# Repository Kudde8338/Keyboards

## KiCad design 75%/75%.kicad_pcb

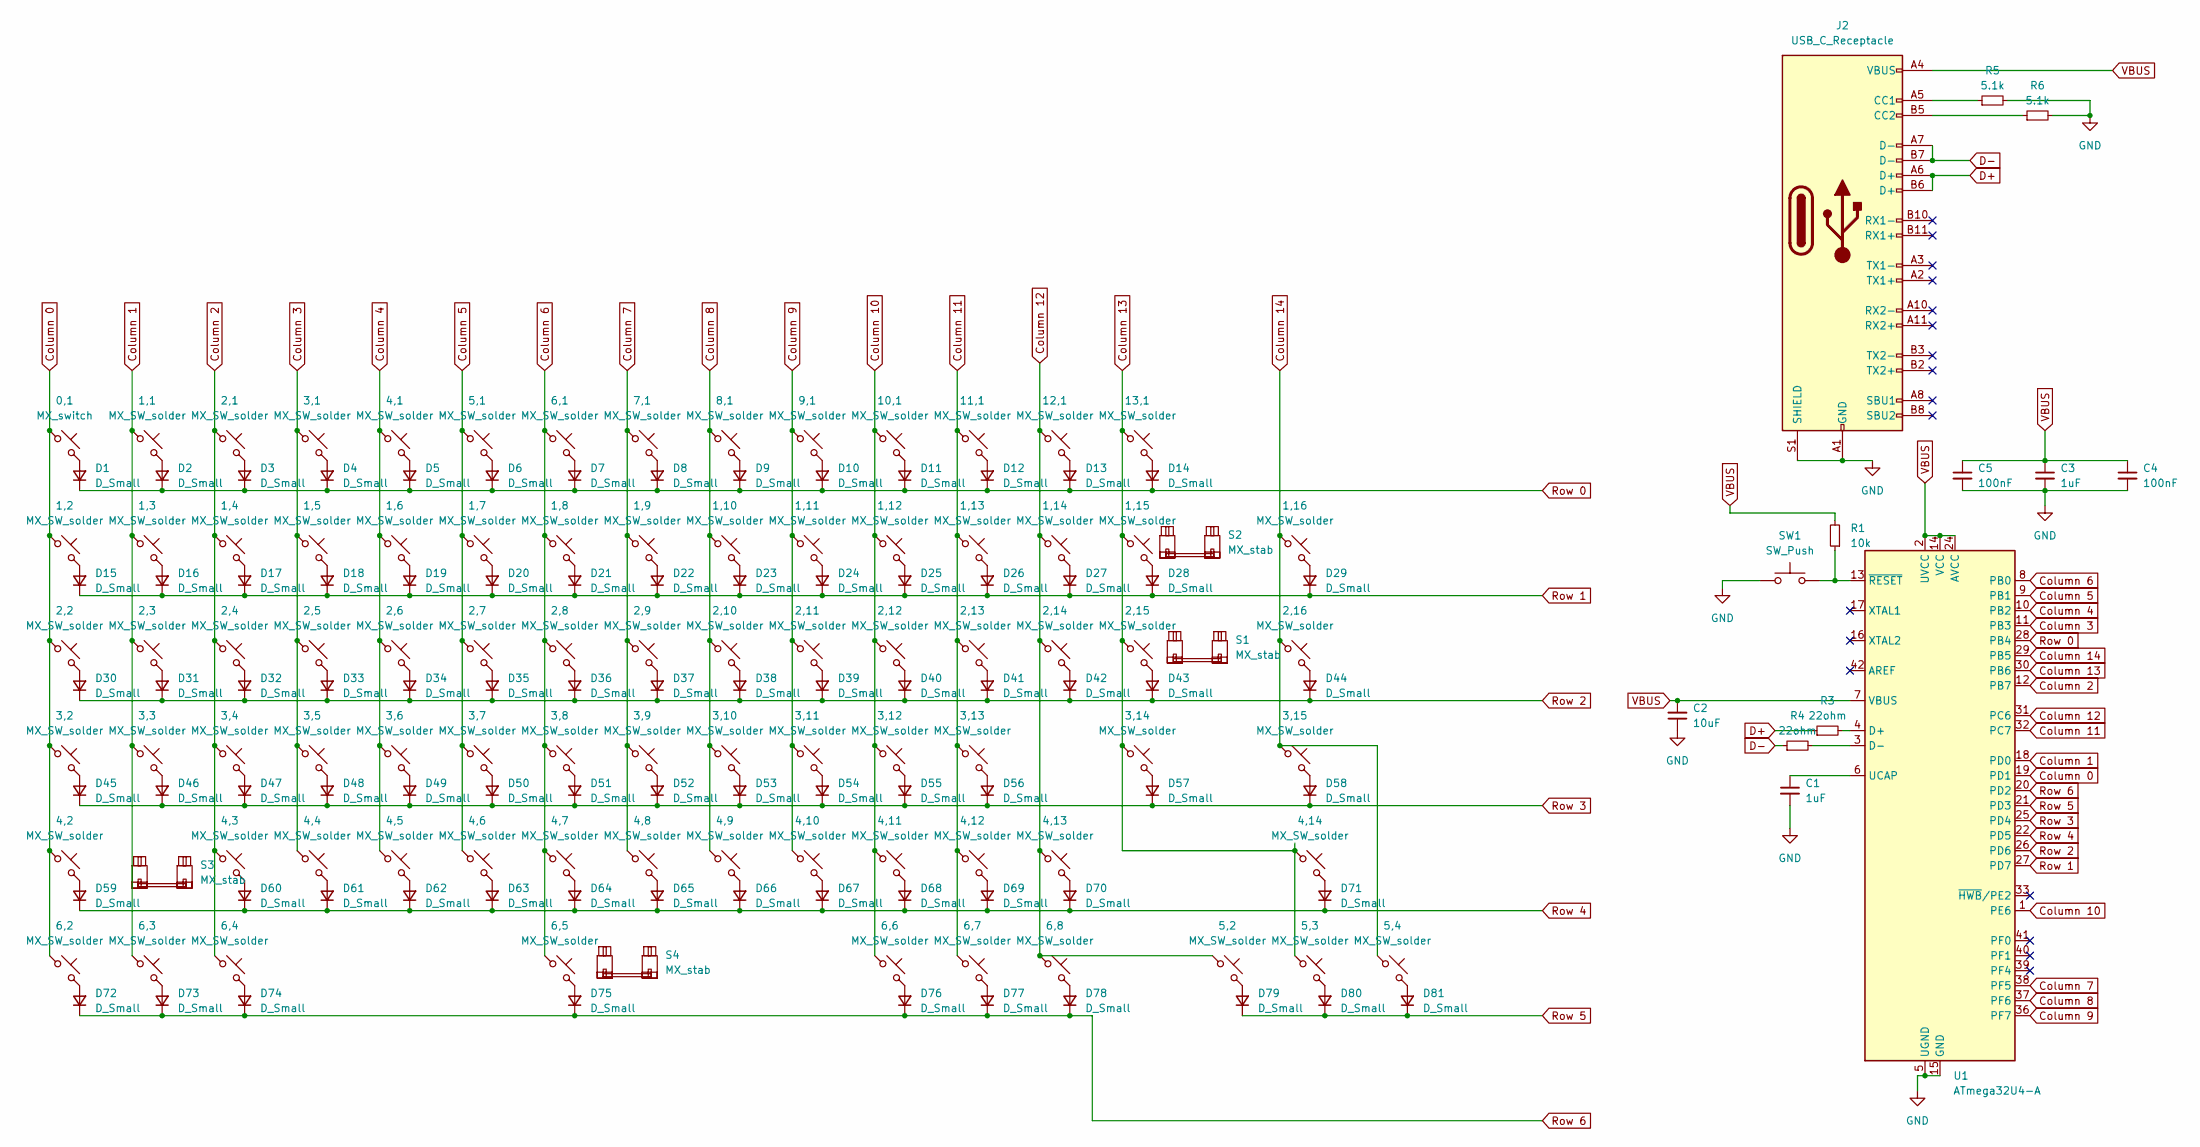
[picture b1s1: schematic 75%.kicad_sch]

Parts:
0,1: MX_switch; SW_MX_1u
1,1, 1,2, 1,3, 1,4, 1,5, 1,6, 1,7, 1,8, 1,9, 1,10, 1,11, 1,12, 1,13, 1,14, 1,15, 1,16, 2,1, 2,3, 2,4, 2,5, 2,6, 2,7, 2,8, 2,9, 2,10, 2,11, 2,12, 2,13, 2,14, 2,16, 3,1, 3,3, 3,4, 3,5, 3,6, 3,7, 3,8, 3,9, 3,10, 3,11, 3,12, 3,13, 3,14, 3,15, 4,1, 4,2, 4,3, 4,4, 4,5, 4,6, 4,7, 4,8, 4,9, 4,10, 4,11, 4,12, 4,14, 5,1, 5,2, 5,3, 5,4, 6,1, 6,5, 6,6, 6,7, 6,8, 7,1, 8,1, 9,1, 10,1, 11,1, 12,1, 13,1: MX_SW_solder; SW_MX_1u
2,2, 2,15: MX_SW_solder; SW_MX_1.5u
3,2, 4,13: MX_SW_solder; SW_MX_1.75u
6,2, 6,3, 6,4: MX_SW_solder; SW_MX_1.25u
C1, C3: 1uF; C_0805_2012Metric
C2: 10uF; C_0805_2012Metric
C4, C5: 100nF; C_0805_2012Metric
D1, D2, D3, D4, D5, D6, D7, D8, D9, D10, D11, D12, D13, D14, D15, D16, D17, D18, D19, D20, D21, D22, D23, D24, D25, D26, D27, D28, D29, D30, D31, D32, D33, D34, D35, D36, D37, D38, D39, D40, D41, D42, D43, D44, D45, D46, D47, D48, D49, D50, D51, D52, D53, D54, D55, D56, D57, D58, D59, D60, D61, D62, D63, D64, D65, D66, D67, D68, D69, D70, D71, D72, D73, D74, D75, D76, D77, D78, D79, D80, D81: D_Small; D_SOD-123
J2: USB_C_Receptacle; USB_C_Receptacle_GCT_USB4105-xx-A_16P_TopMnt_Horizontal
R1: 10k; R_0805_2012Metric
R3, R4: 22ohm; R_0805_2012Metric
R5, R6: 5.1k; R_0805_2012Metric
S1, S3: MX_stab; STAB_MX_P_2.25u
S2: MX_stab; STAB_MX_P_2u
S4: MX_stab; STAB_MX_P_6.25u
SW1: SW_Push; SW_PUSH-12mm
U1: ATmega32U4-A; TQFP-44_10x10mm_P0.8mm

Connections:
Column 0: 0,1.1, 1,2.1, 2,2.1, 3,2.1, 4,2.1, 6,2.1, U1.19 (PD1)
Column 1: 1,1.1, 1,3.1, 2,3.1, 3,3.1, 6,3.1, U1.18 (PD0)
Column 2: 1,4.1, 2,1.1, 2,4.1, 3,4.1, 4,3.1, 6,4.1, U1.12 (PB7)
Column 3: 1,5.1, 2,5.1, 3,1.1, 3,5.1, 4,4.1, U1.11 (PB3)
Column 4: 1,6.1, 2,6.1, 3,6.1, 4,1.1, 4,5.1, U1.10 (PB2)
Column 5: 1,7.1, 2,7.1, 3,7.1, 4,6.1, 5,1.1, U1.9 (PB1)
Column 6: 1,8.1, 2,8.1, 3,8.1, 4,7.1, 6,1.1, 6,5.1, U1.8 (PB0)
Column 7: 1,9.1, 2,9.1, 3,9.1, 4,8.1, 7,1.1, U1.38 (PF5)
Column 8: 1,10.1, 2,10.1, 3,10.1, 4,9.1, 8,1.1, U1.37 (PF6)
Column 9: 1,11.1, 2,11.1, 3,11.1, 4,10.1, 9,1.1, U1.36 (PF7)
Column 10: 1,12.1, 2,12.1, 3,12.1, 4,11.1, 6,6.1, 10,1.1, U1.1 (PE6)
Column 11: 1,13.1, 2,13.1, 3,13.1, 4,12.1, 6,7.1, 11,1.1, U1.32 (PC7)
Column 12: 1,14.1, 2,14.1, 4,13.1, 5,2.1, 6,8.1, 12,1.1, U1.31 (PC6)
Column 13: 1,15.1, 2,15.1, 3,14.1, 4,14.1, 5,3.1, 13,1.1, U1.30 (PB6)
Column 14: 1,16.1, 2,16.1, 3,15.1, 5,4.1, U1.29 (PB5)
D+: J2.A6 (D+), J2.B6 (D+), R3.1
D-: J2.A7 (D-), J2.B7 (D-), R4.1
GND: C1.2, C2.1, C3.2, C4.2, C5.2, J2.A1 (GND), J2.A12 (GND), J2.B1 (GND), J2.B12 (GND), J2.S1 (SHIELD), R5.2, R6.2, SW1.1, U1.5 (UGND), U1.15 (GND), U1.23 (GND), U1.35 (GND), U1.43 (GND)
unnamed: 0,1.2, D1.2 (A)
unnamed: 1,1.2, D2.2 (A)
unnamed: 2,1.2, D3.2 (A)
unnamed: 3,1.2, D4.2 (A)
unnamed: 4,1.2, D5.2 (A)
unnamed: 5,1.2, D6.2 (A)
unnamed: 6,1.2, D7.2 (A)
unnamed: 7,1.2, D8.2 (A)
unnamed: 8,1.2, D9.2 (A)
unnamed: 9,1.2, D10.2 (A)
unnamed: 10,1.2, D11.2 (A)
unnamed: 11,1.2, D12.2 (A)
unnamed: 12,1.2, D13.2 (A)
unnamed: 13,1.2, D14.2 (A)
unnamed: 1,2.2, D15.2 (A)
unnamed: 1,3.2, D16.2 (A)
unnamed: 1,4.2, D17.2 (A)
unnamed: 1,5.2, D18.2 (A)
unnamed: 1,6.2, D19.2 (A)
unnamed: 1,7.2, D20.2 (A)
unnamed: 1,8.2, D21.2 (A)
unnamed: 1,9.2, D22.2 (A)
unnamed: 1,10.2, D23.2 (A)
unnamed: 1,11.2, D24.2 (A)
unnamed: 1,12.2, D25.2 (A)
unnamed: 1,13.2, D26.2 (A)
unnamed: 1,14.2, D27.2 (A)
unnamed: 1,15.2, D28.2 (A)
unnamed: 1,16.2, D29.2 (A)
unnamed: 2,2.2, D30.2 (A)
unnamed: 2,3.2, D31.2 (A)
unnamed: 2,4.2, D32.2 (A)
unnamed: 2,5.2, D33.2 (A)
unnamed: 2,6.2, D34.2 (A)
unnamed: 2,7.2, D35.2 (A)
unnamed: 2,8.2, D36.2 (A)
unnamed: 2,9.2, D37.2 (A)
unnamed: 2,10.2, D38.2 (A)
unnamed: 2,11.2, D39.2 (A)
unnamed: 2,12.2, D40.2 (A)
unnamed: 2,13.2, D41.2 (A)
unnamed: 2,14.2, D42.2 (A)
unnamed: 2,15.2, D43.2 (A)
unnamed: 2,16.2, D44.2 (A)
unnamed: 3,2.2, D45.2 (A)
unnamed: 3,3.2, D46.2 (A)
unnamed: 3,4.2, D47.2 (A)
unnamed: 3,5.2, D48.2 (A)
unnamed: 3,6.2, D49.2 (A)
unnamed: 3,7.2, D50.2 (A)
unnamed: 3,8.2, D51.2 (A)
unnamed: 3,9.2, D52.2 (A)
unnamed: 3,10.2, D53.2 (A)
unnamed: 3,11.2, D54.2 (A)
unnamed: 3,12.2, D55.2 (A)
unnamed: 3,13.2, D56.2 (A)
unnamed: 3,14.2, D57.2 (A)
unnamed: 3,15.2, D58.2 (A)
unnamed: 4,2.2, D59.2 (A)
unnamed: 4,3.2, D60.2 (A)
unnamed: 4,4.2, D61.2 (A)
unnamed: 4,5.2, D62.2 (A)
unnamed: 4,6.2, D63.2 (A)
unnamed: 4,7.2, D64.2 (A)
unnamed: 4,8.2, D65.2 (A)
unnamed: 4,9.2, D66.2 (A)
unnamed: 4,10.2, D67.2 (A)
unnamed: 4,11.2, D68.2 (A)
unnamed: 4,12.2, D69.2 (A)
unnamed: 4,13.2, D70.2 (A)
unnamed: 4,14.2, D71.2 (A)
unnamed: 6,2.2, D72.2 (A)
unnamed: 6,3.2, D73.2 (A)
unnamed: 6,4.2, D74.2 (A)
unnamed: 6,5.2, D75.2 (A)
unnamed: 6,6.2, D76.2 (A)
unnamed: 6,7.2, D77.2 (A)
unnamed: 6,8.2, D78.2 (A)
unnamed: 5,2.2, D79.2 (A)
unnamed: 5,3.2, D80.2 (A)
unnamed: 5,4.2, D81.2 (A)
unnamed: J2.A5 (CC1), R5.1
unnamed: J2.B5 (CC2), R6.1
unnamed: R3.2, U1.4 (D+)
unnamed: R4.2, U1.3 (D-)
unnamed: C1.1, U1.6 (UCAP)
unnamed: R1.1, SW1.2, U1.13 (~RESET)
Row 0: D1.1 (K), D2.1 (K), D3.1 (K), D4.1 (K), D5.1 (K), D6.1 (K), D7.1 (K), D8.1 (K), D9.1 (K), D10.1 (K), D11.1 (K), D12.1 (K), D13.1 (K), D14.1 (K), U1.28 (PB4)
Row 1: D15.1 (K), D16.1 (K), D17.1 (K), D18.1 (K), D19.1 (K), D20.1 (K), D21.1 (K), D22.1 (K), D23.1 (K), D24.1 (K), D25.1 (K), D26.1 (K), D27.1 (K), D28.1 (K), D29.1 (K), U1.27 (PD7)
Row 2: D30.1 (K), D31.1 (K), D32.1 (K), D33.1 (K), D34.1 (K), D35.1 (K), D36.1 (K), D37.1 (K), D38.1 (K), D39.1 (K), D40.1 (K), D41.1 (K), D42.1 (K), D43.1 (K), D44.1 (K), U1.26 (PD6)
Row 3: D45.1 (K), D46.1 (K), D47.1 (K), D48.1 (K), D49.1 (K), D50.1 (K), D51.1 (K), D52.1 (K), D53.1 (K), D54.1 (K), D55.1 (K), D56.1 (K), D57.1 (K), D58.1 (K), U1.25 (PD4)
Row 4: D59.1 (K), D60.1 (K), D61.1 (K), D62.1 (K), D63.1 (K), D64.1 (K), D65.1 (K), D66.1 (K), D67.1 (K), D68.1 (K), D69.1 (K), D70.1 (K), D71.1 (K), U1.22 (PD5)
Row 5: D79.1 (K), D80.1 (K), D81.1 (K), U1.21 (PD3)
Row 6: D72.1 (K), D73.1 (K), D74.1 (K), D75.1 (K), D76.1 (K), D77.1 (K), D78.1 (K), U1.20 (PD2)
VBUS: C2.2, C3.1, C4.1, C5.1, J2.A4 (VBUS), J2.A9 (VBUS), J2.B4 (VBUS), J2.B9 (VBUS), R1.2, U1.2 (UVCC), U1.7 (VBUS), U1.14 (VCC), U1.24 (AVCC), U1.34 (VCC), U1.44 (AVCC)

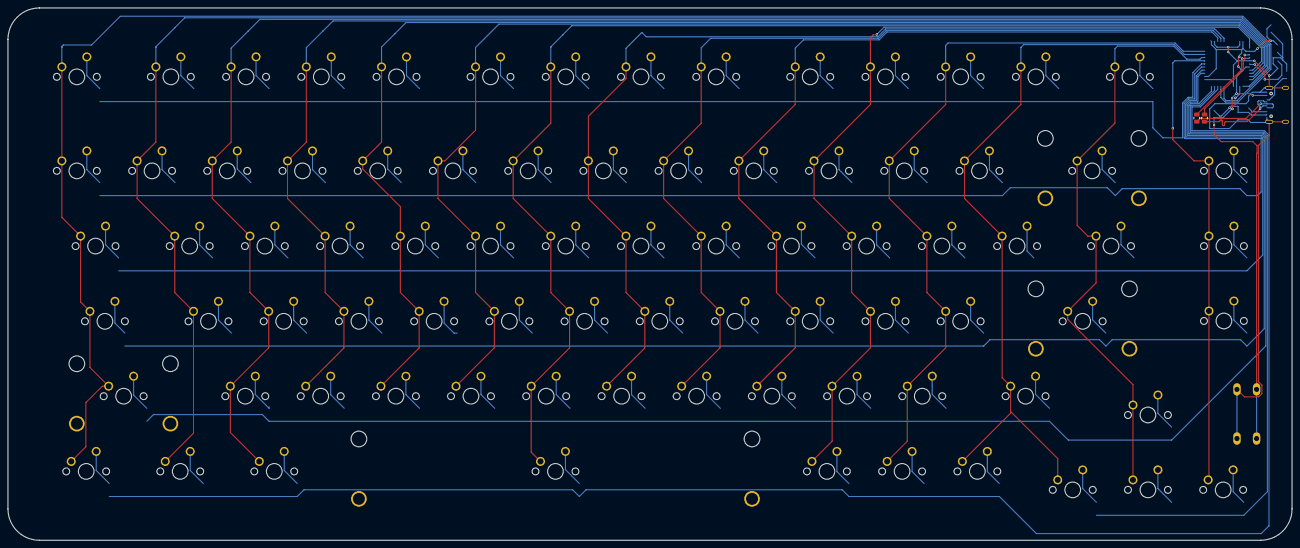
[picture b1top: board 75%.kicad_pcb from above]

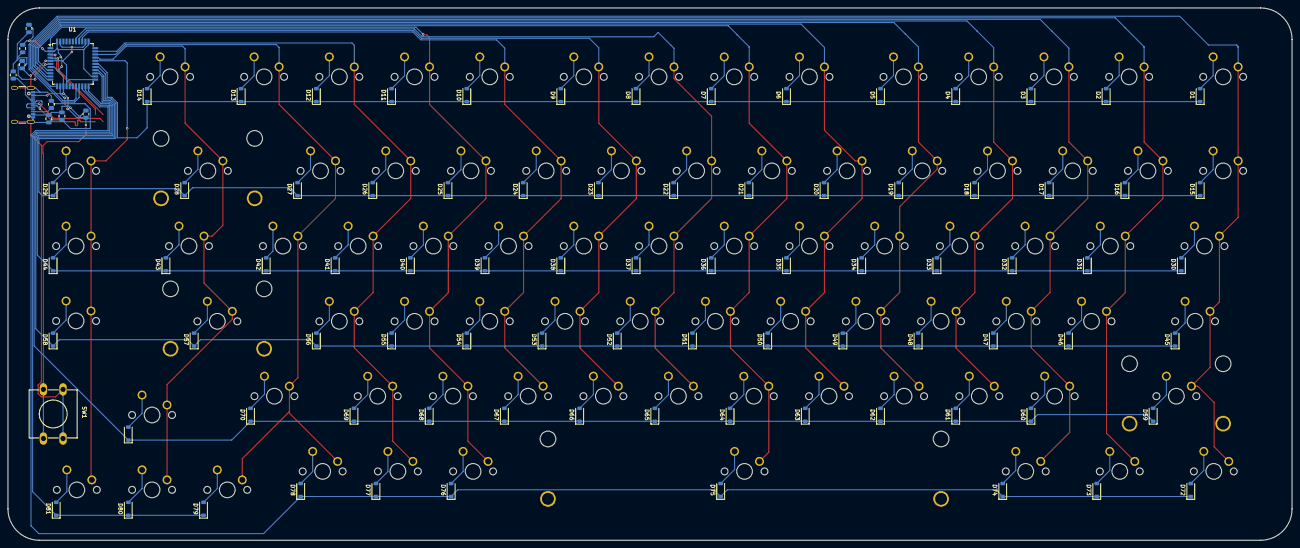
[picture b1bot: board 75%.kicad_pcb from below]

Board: 2 copper layers, 326.7 x 135.4 mm, 179 parts (92 on the bottom side), 113 nets.

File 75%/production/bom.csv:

Designator,Footprint,Quantity,Value,LCSC Part #
"0,1",SW_MX_1u,1,MX_switch,
"1,1, 1,10, 1,11, 1,12, 1,13, 1,14, 1,15, 1,16, 1,2, 1,3, 1,4, 1,5, 1,6, 1,7, 1,8, 1,9, 10,1, 11,1, 12,1, 13,1, 2,1, 2,10, 2,11, 2,12, 2,13, 2,14, 2,16, 2,3, 2,4, 2,5, 2,6, 2,7, 2,8, 2,9, 3,1, 3,10, 3,11, 3,12, 3,13, 3,14, 3,15, 3,3, 3,4, 3,5, 3,6, 3,7, 3,8, 3,9, 4,1, 4,10, 4,11, 4,12, 4,14, 4,2, 4,3, 4,4, 4,5, 4,6, 4,7, 4,8, 4,9, 5,1, 5,2, 5,3, 5,4, 6,1, 6,5, 6,6, 6,7, 6,8, 7,1, 8,1, 9,1",SW_MX_1u,73,MX_SW_solder,
"2,15, 2,2",SW_MX_1.5u,2,MX_SW_solder,
"3,2, 4,13",SW_MX_1.75u,2,MX_SW_solder,
"6,2, 6,3, 6,4",SW_MX_1.25u,3,MX_SW_solder,
"D1, D10, D11, D12, D13, D14, D15, D16, D17, D18, D19, D2, D20, D21, D22, D23, D24, D25, D26, D27, D28, D29, D3, D30, D31, D32, D33, D34, D35, D36, D37, D38, D39, D4, D40, D41, D42, D43, D44, D45, D46, D47, D48, D49, D5, D50, D51, D52, D53, D54, D55, D56, D57, D58, D59, D6, D60, D61, D62, D63, D64, D65, D66, D67, D68, D69, D7, D70, D71, D72, D73, D74, D75, D76, D77, D78, D79, D8, D80, D81, D9",D_SOD-123,81,D_Small,
"S1, S3",STAB_MX_P_2.25u,2,MX_stab,
S2,STAB_MX_P_2u,1,MX_stab,
S4,STAB_MX_P_6.25u,1,MX_stab,
U1,TQFP-44_10x10mm_P0.8mm,1,ATmega32U4-A,

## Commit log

2024-10-11 Uploaded project
2024-10-11 updated the via
2024-10-11 Add submodules
2024-10-12 quick fixes
2024-10-16 latest
